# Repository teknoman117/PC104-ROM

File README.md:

# PC104-ROM

A carrier board for a 32 pin JEDEC ROM device. Used to override the internal ROM of the Technologic Systems TS-3100.

The TS-3100 does not have a compliant PC/104 connector, as the DMA pins are replaced with some internal signals. This board takes advantage of that by allowing an external ROM to be selected from some of these signals.

Licensed under CC-BY-SA 4.0

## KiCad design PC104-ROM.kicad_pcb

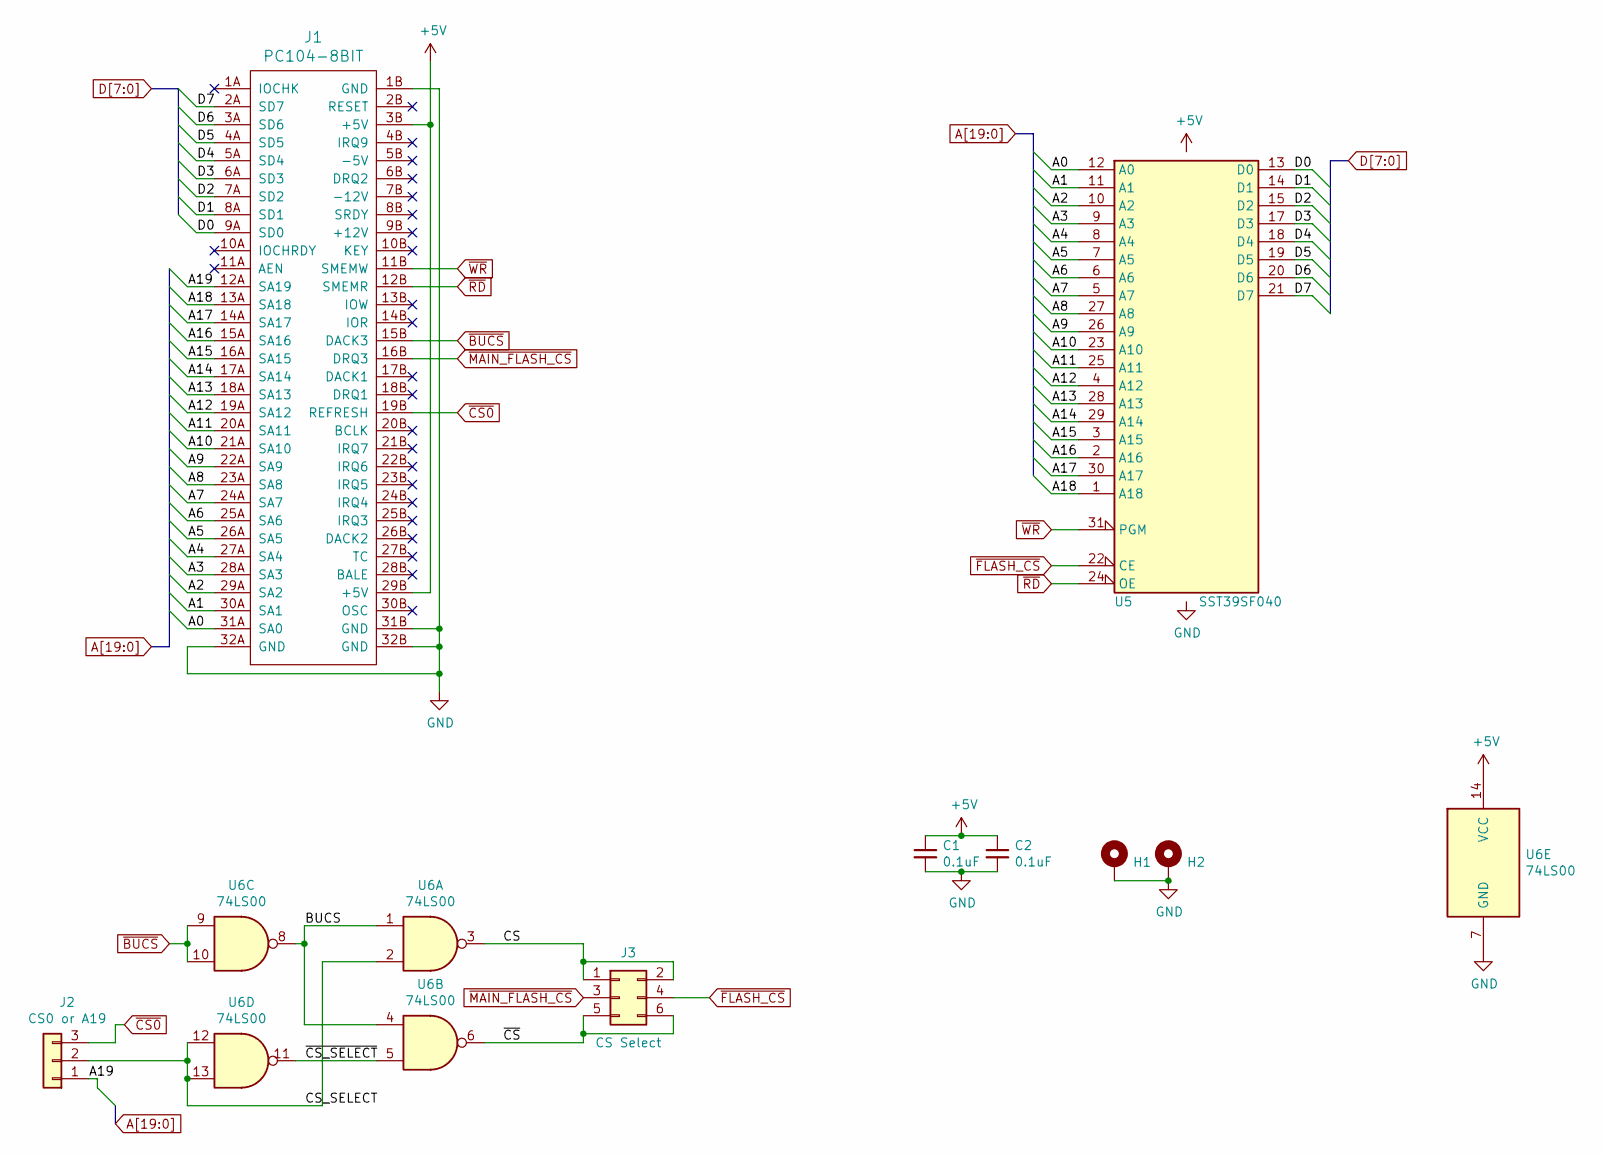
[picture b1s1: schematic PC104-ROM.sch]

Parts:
C1, C2: 0.1uF; C_Disc_D5.0mm_W2.5mm_P2.50mm
H1, H2: MountingHole_3.2mm_M3_Pad
J1: PC104-8BIT; PC104-8bit
J2: CS0 or A19; PinHeader_1x03_P2.54mm_Vertical
J3: CS Select; PinHeader_2x03_P2.54mm_Vertical
U5: SST39SF040; DIP-32_W15.24mm_Socket
U6: 74LS00; DIP-14_W7.62mm_Socket

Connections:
+5V: C1.1, C2.1, J1.3B (+5V), J1.29B (+5V), U5.32 (VCC), U6.14 (VCC)
/A0: J1.31A (SA0), U5.12 (A0)
/A1: J1.30A (SA1), U5.11 (A1)
/A2: J1.29A (SA2), U5.10 (A2)
/A3: J1.28A (SA3), U5.9 (A3)
/A4: J1.27A (SA4), U5.8 (A4)
/A5: J1.26A (SA5), U5.7 (A5)
/A6: J1.25A (SA6), U5.6 (A6)
/A7: J1.24A (SA7), U5.5 (A7)
/A8: J1.23A (SA8), U5.27 (A8)
/A9: J1.22A (SA9), U5.26 (A9)
/A10: J1.21A (SA10), U5.23 (A10)
/A11: J1.20A (SA11), U5.25 (A11)
/A12: J1.19A (SA12), U5.4 (A12)
/A13: J1.18A (SA13), U5.28 (A13)
/A14: J1.17A (SA14), U5.29 (A14)
/A15: J1.16A (SA15), U5.3 (A15)
/A16: J1.15A (SA16), U5.2 (A16)
/A17: J1.14A (SA17), U5.30 (A17)
/A18: J1.13A (SA18), U5.1 (A18)
/A19: J1.12A (SA19), J2.1
/BUCS: U6.1, U6.4, U6.8
/CS: J3.1, J3.2, U6.3
/CS_SELECT: J2.2, U6.2, U6.12, U6.13
/D0: J1.9A (SD0), U5.13 (D0)
/D1: J1.8A (SD1), U5.14 (D1)
/D2: J1.7A (SD2), U5.15 (D2)
/D3: J1.6A (SD3), U5.17 (D3)
/D4: J1.5A (SD4), U5.18 (D4)
/D5: J1.4A (SD5), U5.19 (D5)
/D6: J1.3A (SD6), U5.20 (D6)
/D7: J1.2A (SD7), U5.21 (D7)
/~CS: J3.5, J3.6, U6.6
/~CS_SELECT: U6.5, U6.11
GND: C1.2, C2.2, H1.1, H2.1, J1.1B (GND), J1.31B (GND), J1.32A (GND), J1.32B (GND), U5.16 (GND), U6.7 (GND)
~BUCS: J1.15B (DACK3), U6.9, U6.10
~CS0: J1.19B (REFRESH), J2.3
~FLASH_CS: J3.4, U5.22 (CE)
~MAIN_FLASH_CS: J1.16B (DRQ3), J3.3
~RD: J1.12B (SMEMR), U5.24 (OE)
~WR: J1.11B (SMEMW), U5.31 (PGM)

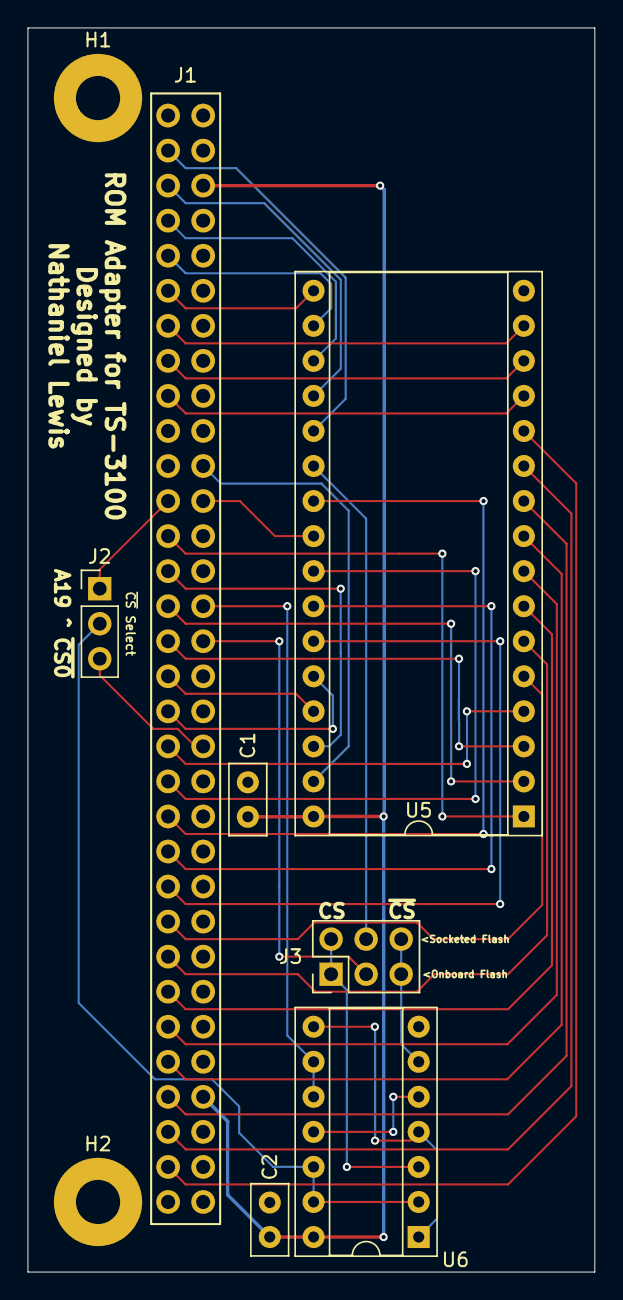
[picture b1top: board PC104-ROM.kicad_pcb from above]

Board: 2 copper layers, 41.1 x 90.2 mm, 9 parts (0 on the bottom side), 41 nets.

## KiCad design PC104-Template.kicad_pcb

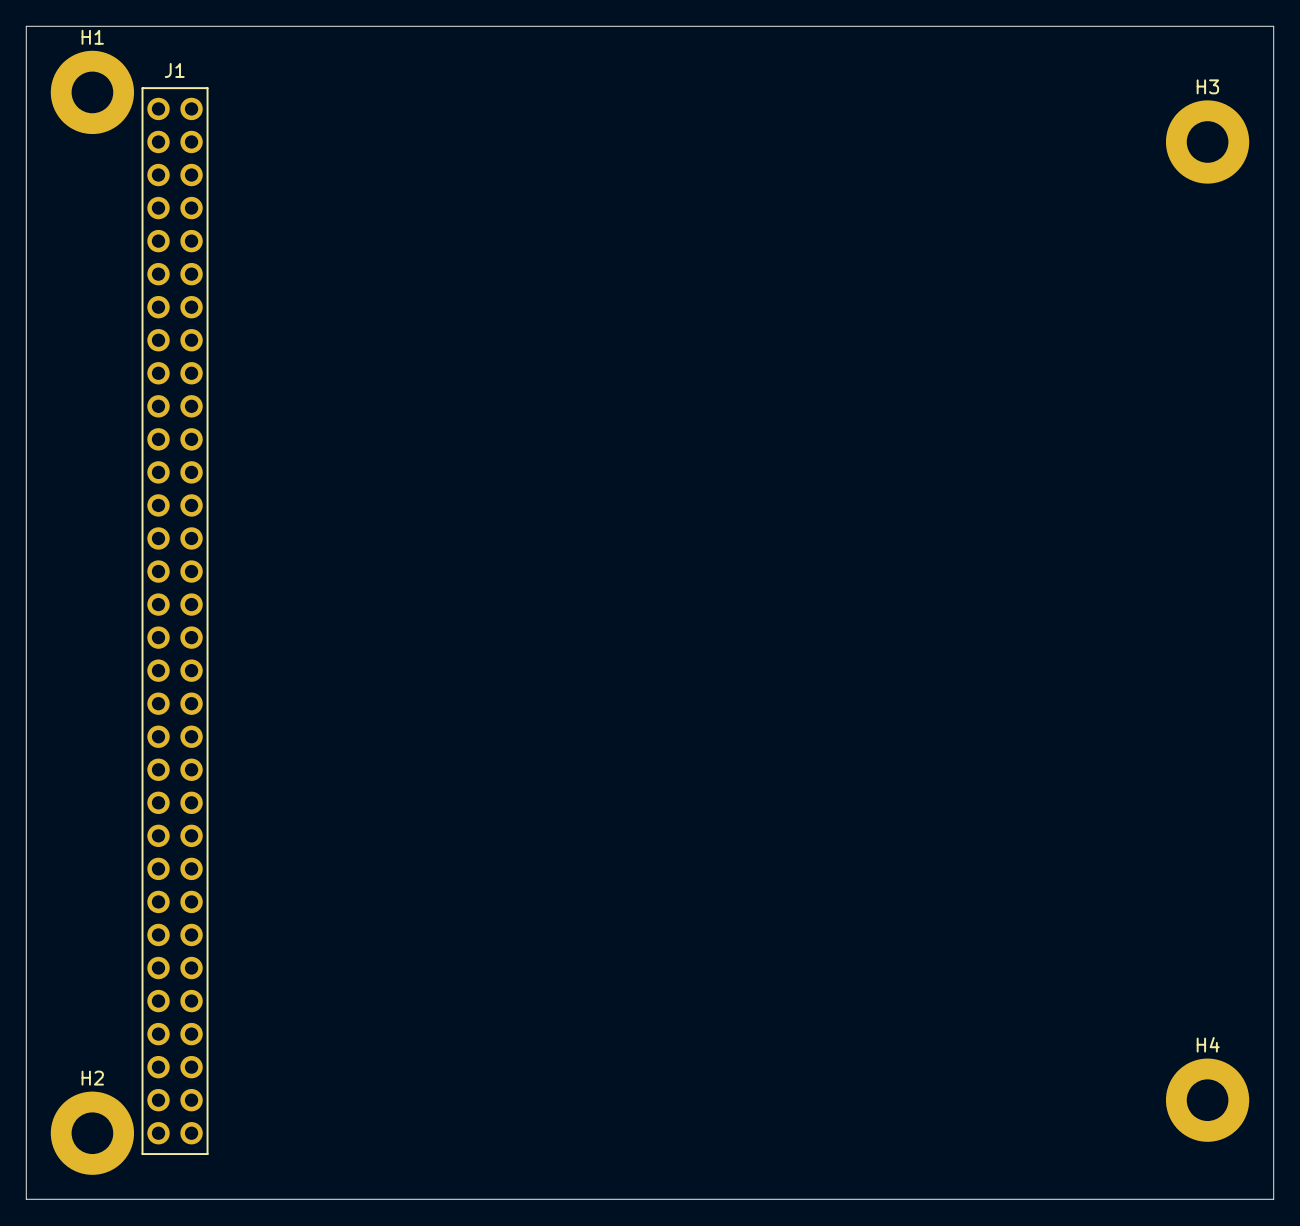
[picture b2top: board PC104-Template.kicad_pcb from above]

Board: 2 copper layers, 95.9 x 90.2 mm, 5 parts (0 on the bottom side), 2 nets, no tracks yet.

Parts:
H1, H2, H3, H4: MountingHole_3.2mm_M3_Pad
J1: PC104-8BIT; PC104-8bit

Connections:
+5V: J1.3B, J1.29B
GND: H1.1, H2.1, H3.1, H4.1, J1.1B, J1.31B, J1.32A, J1.32B

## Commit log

2020-11-28 add KiCad-Lib
2021-08-30 add gerber files for revision 1.0
2021-08-30 Add readme
2021-08-30 Licensed under CC-BY-SA 4.0
